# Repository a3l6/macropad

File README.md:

# a3l6cGFk

## Inspiration
I wanted to have a macropad and I wanted to participate in a Hackclub event because I wish I discovered it earlier.

## Hardest Challenges Faced
I had to restart my PCB 3 separate times. So that was frustrating. I also don't full understand 3D-modelling so that's why my design is just a plate underneath the PCB.

## Other fun facts
The name a3l6cGFK is base64 for kyzpad. Kyz comes from my old clash of clans name that I converted to base64 to not look like something else. Which was not the intention when I used kyz, I just saw someone who raided me and changed my name to theirs.

## BOM
- 6x MX-Style Switches (Gateron Milky Yellows)
- 1x 0.96 inch OLED
- 6x Blank DSA Caps
- 1x WS2812B Neopixel
- 6x 1N4148 Diodes
- 1x Seeed XIAO PR2040 through-hole
- 5x Screws
- 1x PCB

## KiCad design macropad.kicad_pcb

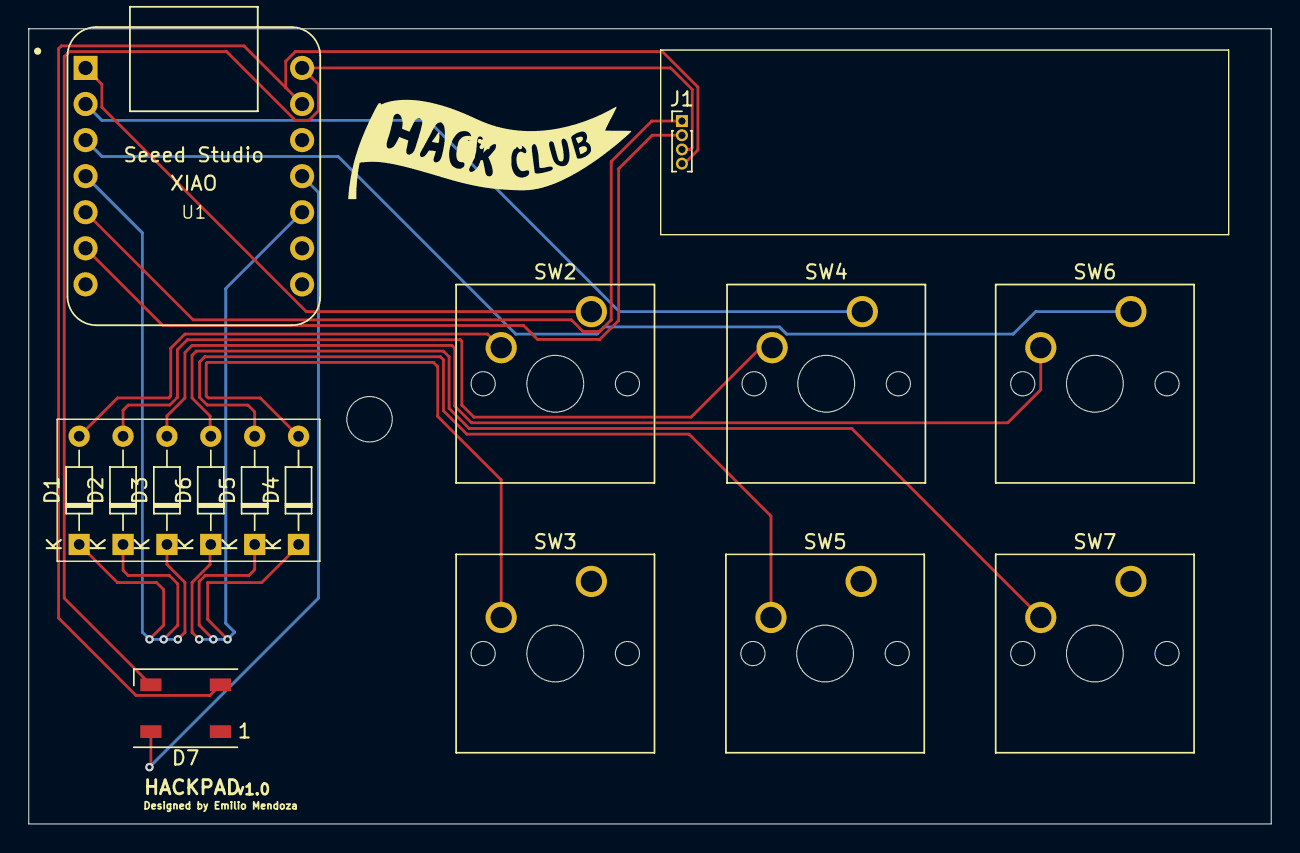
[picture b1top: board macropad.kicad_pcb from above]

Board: 2 copper layers, 87.5 x 56.0 mm, 15 parts (0 on the bottom side), 16 nets.

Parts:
D1, D2, D3, D4, D5, D6: D; D_DO-34_SOD68_P7.62mm_Horizontal
D7: NeoPixel_THT; LED_WS2812B_PLCC4_5.0x5.0mm_P3.2mm
J1: Oled Pins; PinHeader_1x04_P1.00mm_Vertical
SW2, SW3, SW4, SW5, SW6, SW7: SW_Push; SW_Cherry_MX_1.00u_PCB
U1: Seeed Studio XIAO SAMD21; XIAO-Generic-Thruhole-14P-2.54-21X17.8MM

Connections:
Col1: SW2.1, SW3.1, U1.1 (PA02_A0_D0)
Col2: SW4.1, SW5.1, U1.2 (PA4_A1_D1)
Col3: SW6.1, SW7.1, U1.3 (PA10_A2_D2)
GND: D7.2 (GND), J1.4, U1.13 (GND)
NEOPIXEL: D7.4 (DIN), U1.11 (PA6_A10_D10_MOSI)
unnamed: D1.2 (A), SW2.2
unnamed: D2.2 (A), SW4.2
unnamed: D3.2 (A), SW6.2
unnamed: D4.2 (A), SW3.2
unnamed: D5.2 (A), SW5.2
unnamed: D6.2 (A), SW7.2
Row1: D1.1 (K), D2.1 (K), D3.1 (K), U1.4 (PA11_A3_D3)
Row2: D4.1 (K), D5.1 (K), D6.1 (K), U1.10 (PA5_A9_D9_MISO)
SCL: J1.2, U1.6 (PA9_A5_D5_SCL)
SDA: J1.1, U1.5 (PA8_A4_D4_SDA)
VCC: D7.3 (VDD), J1.3, U1.14 (5V)

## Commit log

2024-10-15 started schematic
2024-10-16 Restarted PCB
2024-10-17 Restarting PCB again
2024-10-19 Finished pcb
2024-10-23 Syncing
